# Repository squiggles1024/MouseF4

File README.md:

# Custom Gaming Mouse Project

One of my earlier embedded systems projects. A custom gaming mouse with up to 22 programmable buttons. The firmware is a bit rough around the edges, but I learned a lot about wired USB in the process of coding it.
I wrote a short Python script that communicates new settings to a USB endpoint dedicated to this purpose. 

This iteration implements 14 buttons, a mouse wheel, programmable DPI from 100 to 10000, a tricolored LED with 4 flashing modes, and button keybinds saved in an eeprom.

PCB is my own design featuring an STM32F4 microcontroller which I flashed using a J-Link SEGGER. The PMW3360 motion sensor was purchased as a COTs module. I would have liked to include this on the main PCBA, but the manufacturer was unrespsonsive to my emails and they don't stock the part openly at online retailers like digikey and mouser. The complete BOM and schematics are part of this repository

The 3D printed housing (also my design) was glued to the base plate with E6000. Not a particularly robust mechanical design, but it worked for me. The main issue with this is that, because I didn't write a custom bootloader, the device can no longer be programmed again. This isn't a huge issue, but the mouse wheel you see in the photo is actually "backwards" (Scrolling forward will scroll down, and scrolling backward will scroll up). This is an easy firmware fix, but I can no longer access the JTAG pins or BOOT switch. 

The LED can't really be seen in normal operation, though it can serve as a visual cue that new settings were successfully programmed when changing the keybinds using the python script.

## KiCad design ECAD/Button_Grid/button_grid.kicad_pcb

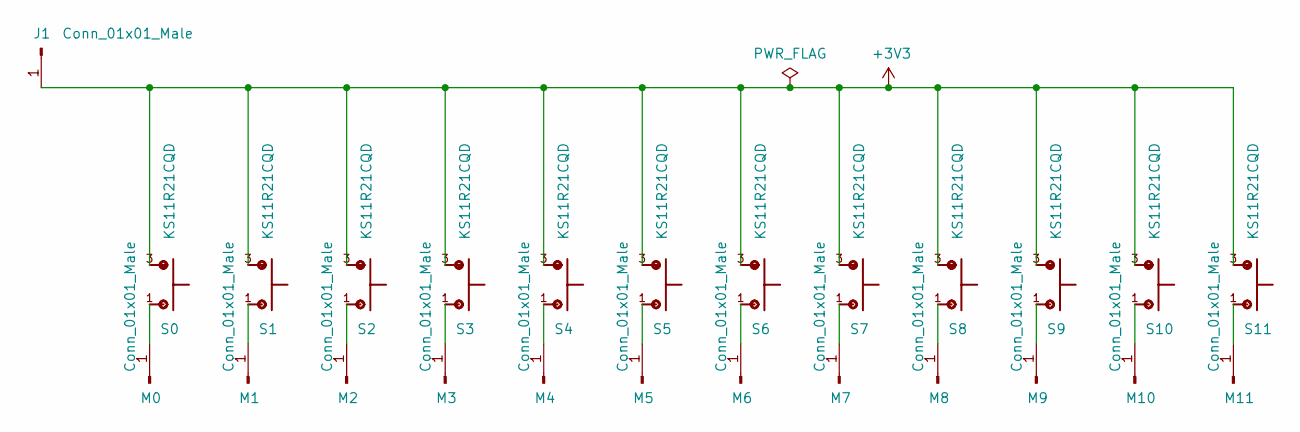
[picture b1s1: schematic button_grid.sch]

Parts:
J1: Conn_01x01_Male; PinHeader_1x01_P2.54mm_Vertical
M0, M1, M2, M3, M4, M5, M6, M7, M8, M9, M10, M11: Conn_01x01_Male; PinHeader_1x01_P2.54mm_Vertical
S0, S1, S2, S3, S4, S5, S6, S7, S8, S9, S10, S11: KS11R21CQD; SW_KS11R21CQD

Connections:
+3V3: J1.1, S0.3, S1.3, S2.3, S3.3, S4.3, S5.3, S6.3, S7.3, S8.3, S9.3, S10.3, S11.3
unnamed: M0.1, S0.1
unnamed: M1.1, S1.1
unnamed: M2.1, S2.1
unnamed: M3.1, S3.1
unnamed: M4.1, S4.1
unnamed: M5.1, S5.1
unnamed: M6.1, S6.1
unnamed: M7.1, S7.1
unnamed: M8.1, S8.1
unnamed: M9.1, S9.1
unnamed: M10.1, S10.1
unnamed: M11.1, S11.1

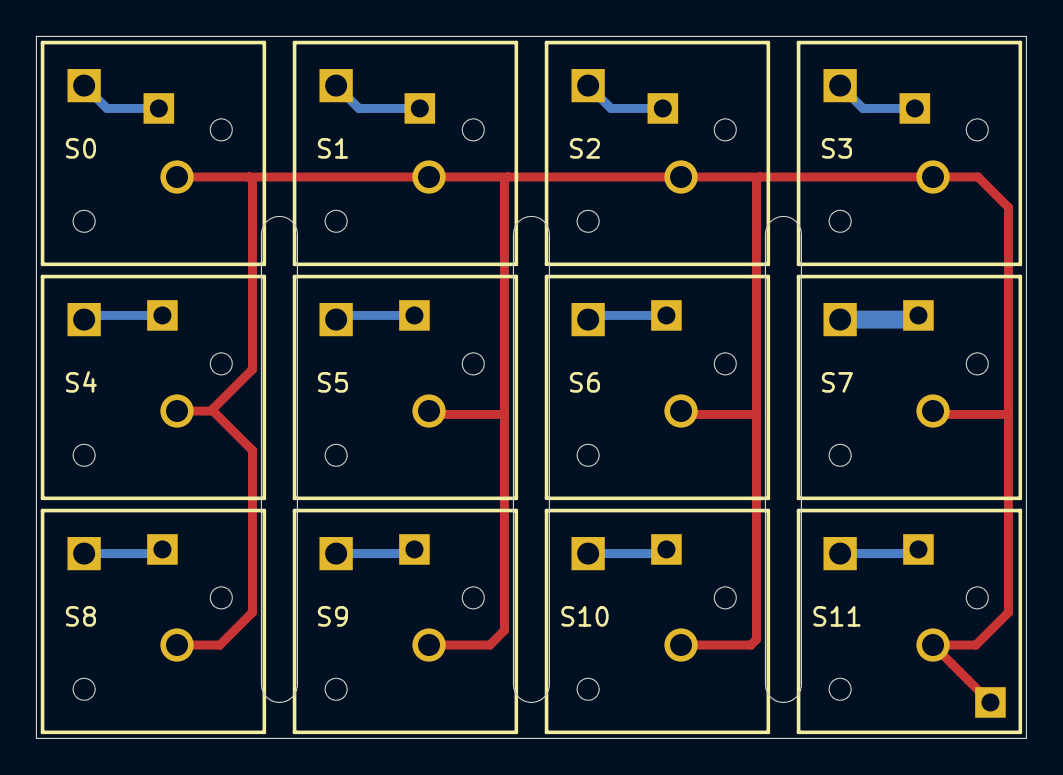
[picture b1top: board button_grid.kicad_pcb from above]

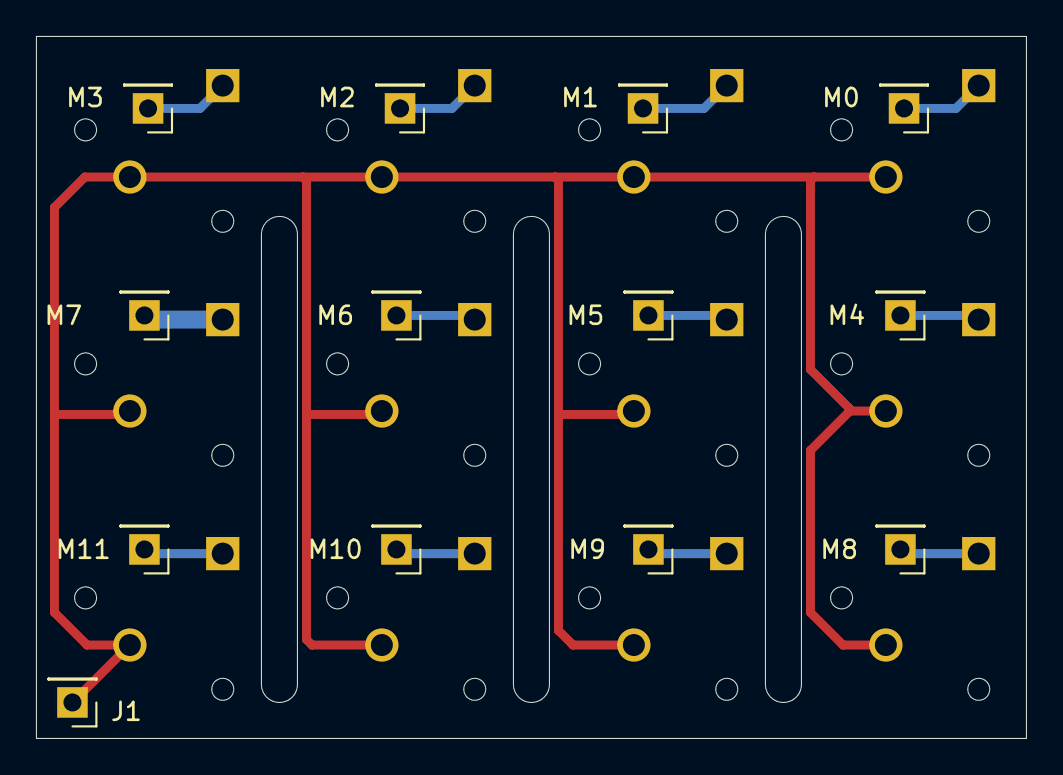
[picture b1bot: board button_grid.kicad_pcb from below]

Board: 2 copper layers, 55.0 x 39.0 mm, 25 parts (13 on the bottom side), 13 nets.

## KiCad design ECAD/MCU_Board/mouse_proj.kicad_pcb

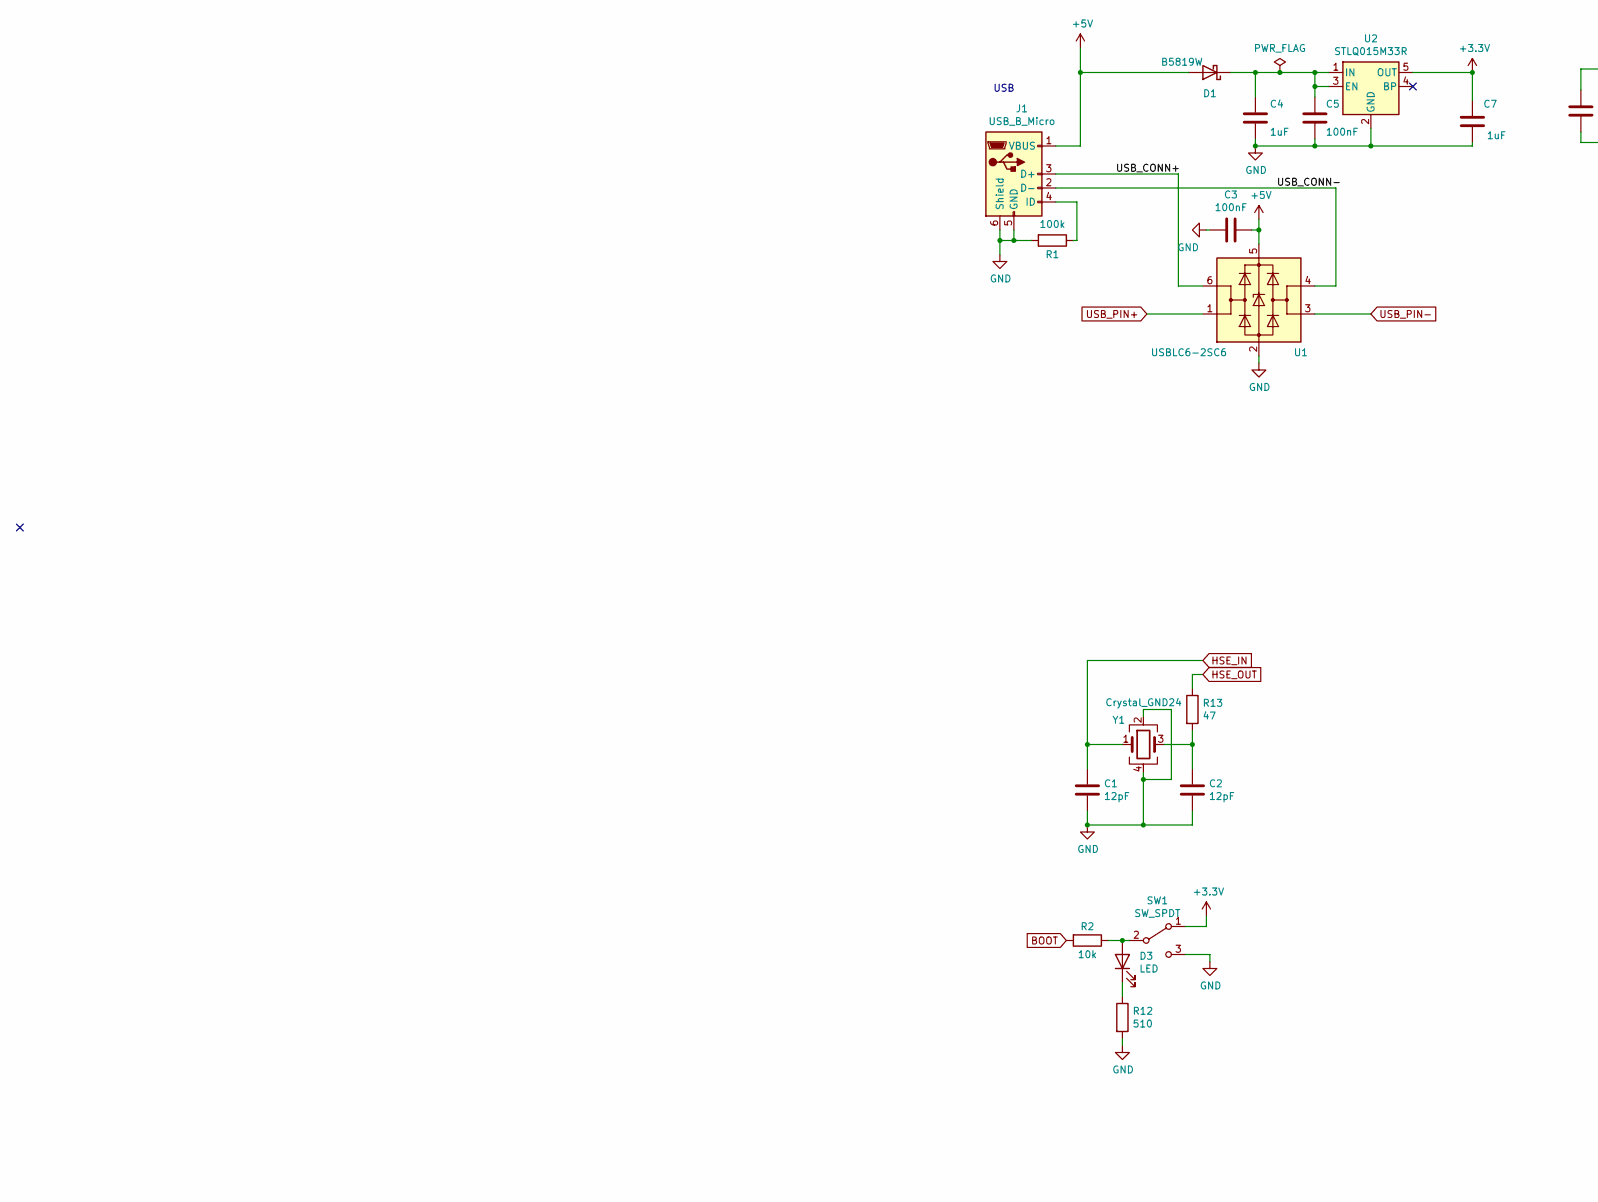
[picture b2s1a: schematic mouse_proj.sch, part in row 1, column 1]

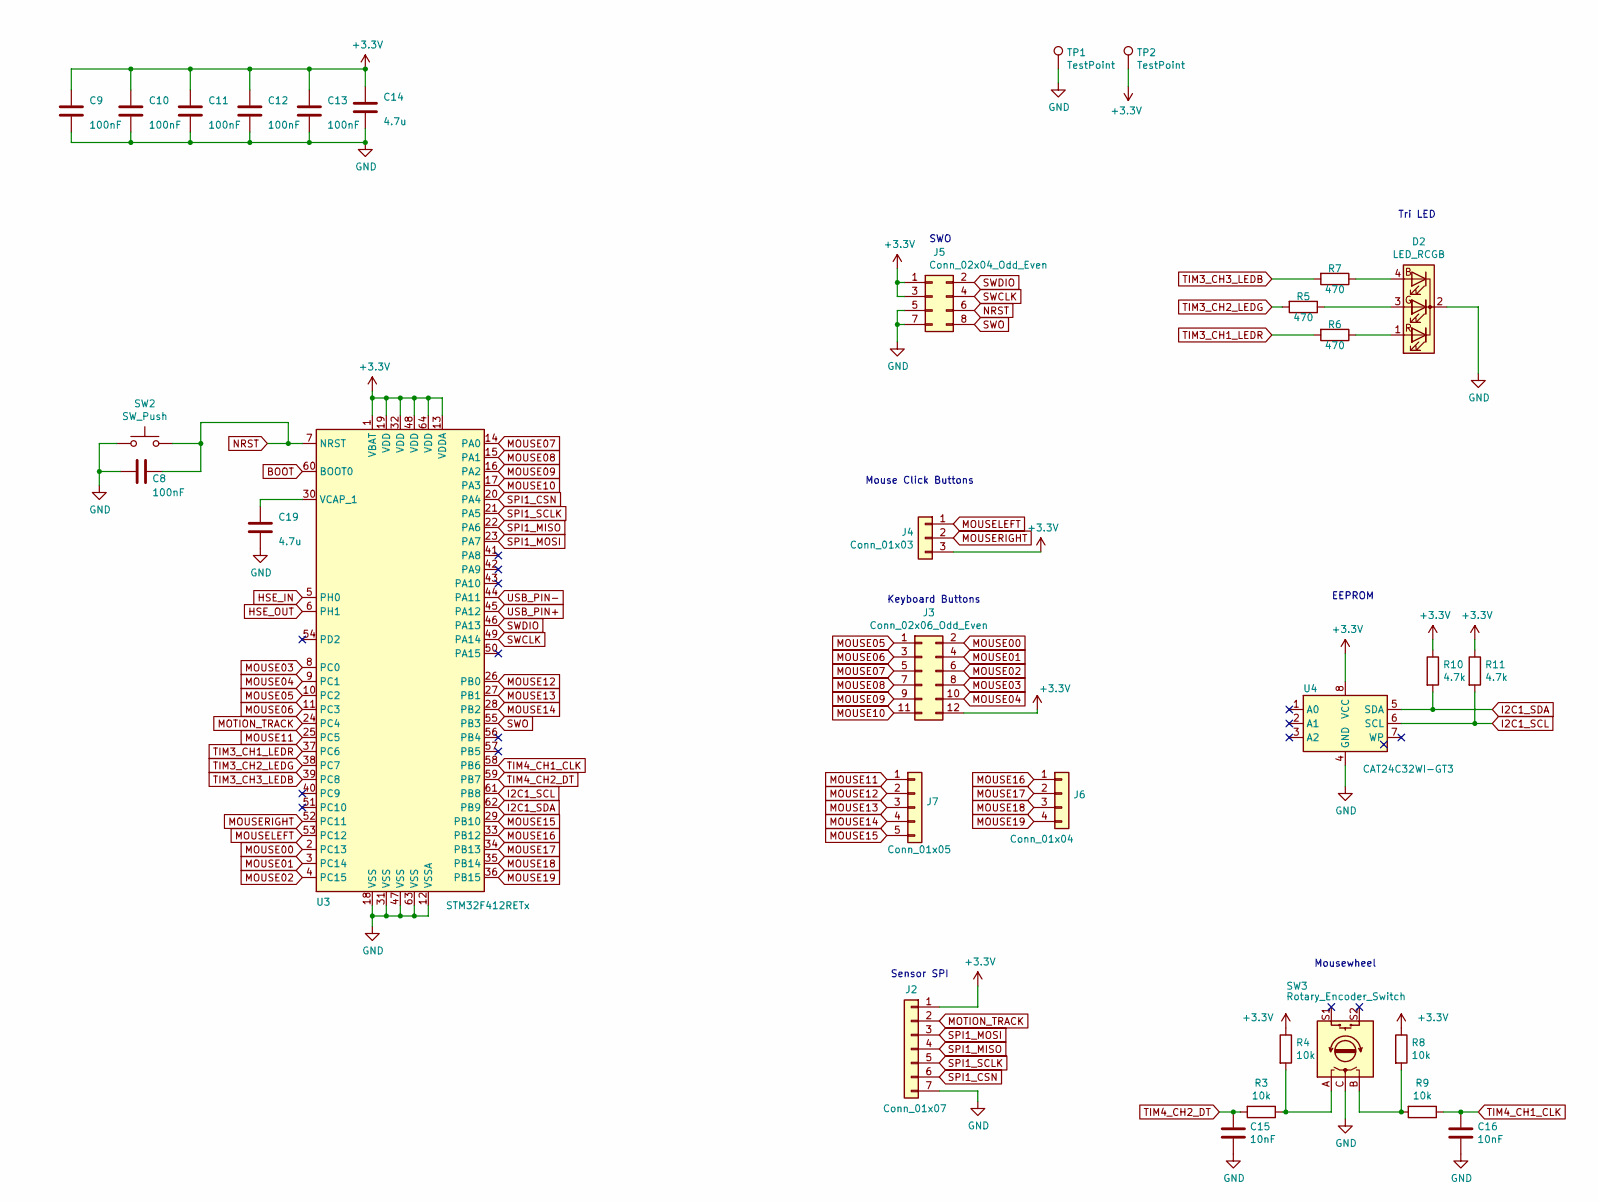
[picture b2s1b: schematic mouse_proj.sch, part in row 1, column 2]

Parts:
C1, C2: 12pF; C_0402_1005Metric; LCSC Part # C26406
C3, C5: 100nF; C_0603_1608Metric; LCSC Part # C14663
C4: 1uF; C_0603_1608Metric; LCSC Part # C15849
C7: 1uF; C_0402_1005Metric; LCSC Part # C52923
C8, C9, C10, C11, C12, C13: 100nF; C_0402_1005Metric; LCSC Part # C307331
C14, C19: 4.7u; C_0402_1005Metric; LCSC Part # C23733
C15, C16: 10nF; C_0402_1005Metric; LCSC Part # C15195
D1: B5819W; D_SOD-123; LCSC Part # C8598
D2: LED_RCGB; LED_D5.0mm-4_RGB_Wide_Pins
D3: LED; D_0603_1608Metric; LCSC Part # C2286
J1: USB_B_Micro; USB_Micro-B_Molex-105017-0001; LCSC Part # C132563
J2: Conn_01x07; PinHeader_1x07_P2.54mm_Vertical
J3: Conn_02x06_Odd_Even; PinHeader_2x06_P2.54mm_Vertical
J4: Conn_01x03; PinHeader_1x03_P2.54mm_Vertical
J5: Conn_02x04_Odd_Even; PinHeader_2x04_P2.54mm_Vertical
J6: Conn_01x04; PinHeader_1x04_P2.54mm_Vertical
J7: Conn_01x05; PinHeader_1x05_P2.54mm_Vertical
R1: 100k; R_0402_1005Metric; LCSC Part # C25741
R2, R3, R4, R8, R9: 10k; R_0402_1005Metric; LCSC Part # C25744
R5, R6, R7: 470; R_0402_1005Metric; LCSC Part # C25117
R10, R11: 4.7k; R_0402_1005Metric; LCSC Part # C25900
R12: 510; R_0402_1005Metric; LCSC Part # C25123
R13: 47; R_0402_1005Metric; LCSC Part # C25117
SW1: SW_SPDT; SW_SPDT_PCM12
SW2: SW_Push; SW_PUSH_6mm_H5mm
SW3: Rotary_Encoder_Switch; RotaryEncoder_Alps_EC11E-Switch_Vertical_H20mm
TP1, TP2: TestPoint; TestPoint_THTPad_D3.0mm_Drill1.5mm
U1: USBLC6-2SC6; SOT-23-6; LCSC Part # C7519
U2: STLQ015M33R; SOT-23-5; LCSC Part # C136154
U3: STM32F412RETx; LQFP-64_10x10mm_P0.5mm; LCSC Part # C89374
U4: CAT24C32WI-GT3; SOIC-8_3.9x4.9mm_P1.27mm; LCSC Part # C81193
Y1: Crystal_GND24; Crystal_SMD_3225-4Pin_3.2x2.5mm; LCSC Part # C13738

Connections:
+3V3: C7.1, C9.1, C10.1, C11.1, C12.1, C13.1, C14.1, J2.1, J3.12, J4.3, J5.1, J5.3, R4.1, R8.1, R10.1, R11.1, SW1.1 (A), TP2.1, U2.5 (OUT), U3.1 (VBAT), U3.13 (VDDA), U3.19 (VDD), U3.32 (VDD), U3.48 (VDD), U3.64 (VDD), U4.8 (VCC)
+5V: C3.1, D1.2 (A), J1.1 (VBUS), U1.5 (VBUS)
/USB_CONN+: J1.3 (D+), U1.6 (I/O1)
/USB_CONN-: J1.2 (D-), U1.4 (I/O2)
BOOT: R2.2, U3.60 (BOOT0)
GND: C1.2, C2.2, C3.2, C4.2, C5.2, C7.2, C8.2, C9.2, C10.2, C11.2, C12.2, C13.2, C14.2, C15.2, C16.2, C19.2, D2.2 (K), J1.5 (GND), J1.6 (Shield), J2.7, J5.5, J5.7, R1.2, R12.2, SW1.3 (C), SW2.1, SW3.C, TP1.1, U1.2 (GND), U2.2 (GND), U3.12 (VSSA), U3.18 (VSS), U3.31 (VSS), U3.47 (VSS), U3.63 (VSS), U4.4 (GND), Y1.2, Y1.4
HSE_IN: C1.1, U3.5 (PH0), Y1.1
HSE_OUT: R13.1, U3.6 (PH1)
I2C1_SCL: R11.2, U3.61 (PB8), U4.6 (SCL)
I2C1_SDA: R10.2, U3.62 (PB9), U4.5 (SDA)
MOTION_TRACK: J2.2, U3.24 (PC4)
MOUSE00: J3.2, U3.2 (PC13)
MOUSE01: J3.4, U3.3 (PC14)
MOUSE02: J3.6, U3.4 (PC15)
MOUSE03: J3.8, U3.8 (PC0)
MOUSE04: J3.10, U3.9 (PC1)
MOUSE05: J3.1, U3.10 (PC2)
MOUSE06: J3.3, U3.11 (PC3)
MOUSE07: J3.5, U3.14 (PA0)
MOUSE08: J3.7, U3.15 (PA1)
MOUSE09: J3.9, U3.16 (PA2)
MOUSE10: J3.11, U3.17 (PA3)
MOUSE11: J7.1, U3.25 (PC5)
MOUSE12: J7.2, U3.26 (PB0)
MOUSE13: J7.3, U3.27 (PB1)
MOUSE14: J7.4, U3.28 (PB2)
MOUSE15: J7.5, U3.29 (PB10)
MOUSE16: J6.1, U3.33 (PB12)
MOUSE17: J6.2, U3.34 (PB13)
MOUSE18: J6.3, U3.35 (PB14)
MOUSE19: J6.4, U3.36 (PB15)
MOUSELEFT: J4.1, U3.53 (PC12)
MOUSERIGHT: J4.2, U3.52 (PC11)
NRST: C8.1, J5.6, SW2.2, U3.7 (NRST)
unnamed: C2.1, R13.2, Y1.3
unnamed: C4.1, C5.1, D1.1 (K), U2.1 (IN), U2.3 (EN)
unnamed: C19.1, U3.30 (VCAP_1)
unnamed: D2.1 (RA), R6.1
unnamed: D2.3 (GA), R5.1
unnamed: D2.4 (BA), R7.1
unnamed: D3.1 (K), R12.1
unnamed: D3.2 (A), R2.1, SW1.2 (B)
unnamed: J1.4 (ID), R1.1
unnamed: R3.1, R4.2, SW3.A
unnamed: R8.2, R9.2, SW3.B
SPI1_CSN: J2.6, U3.20 (PA4)
SPI1_MISO: J2.4, U3.22 (PA6)
SPI1_MOSI: J2.3, U3.23 (PA7)
SPI1_SCLK: J2.5, U3.21 (PA5)
SWCLK: J5.4, U3.49 (PA14)
SWDIO: J5.2, U3.46 (PA13)
SWO: J5.8, U3.55 (PB3)
TIM3_CH1_LEDR: R6.2, U3.37 (PC6)
TIM3_CH2_LEDG: R5.2, U3.38 (PC7)
TIM3_CH3_LEDB: R7.2, U3.39 (PC8)
TIM4_CH1_CLK: C16.1, R9.1, U3.58 (PB6)
TIM4_CH2_DT: C15.1, R3.2, U3.59 (PB7)
USB_PIN+: U1.1 (I/O1), U3.45 (PA12)
USB_PIN-: U1.3 (I/O2), U3.44 (PA11)

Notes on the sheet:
SWO
Tri LED
EEPROM
Mousewheel
Keyboard Buttons
Mouse Click Buttons
Sensor SPI
USB

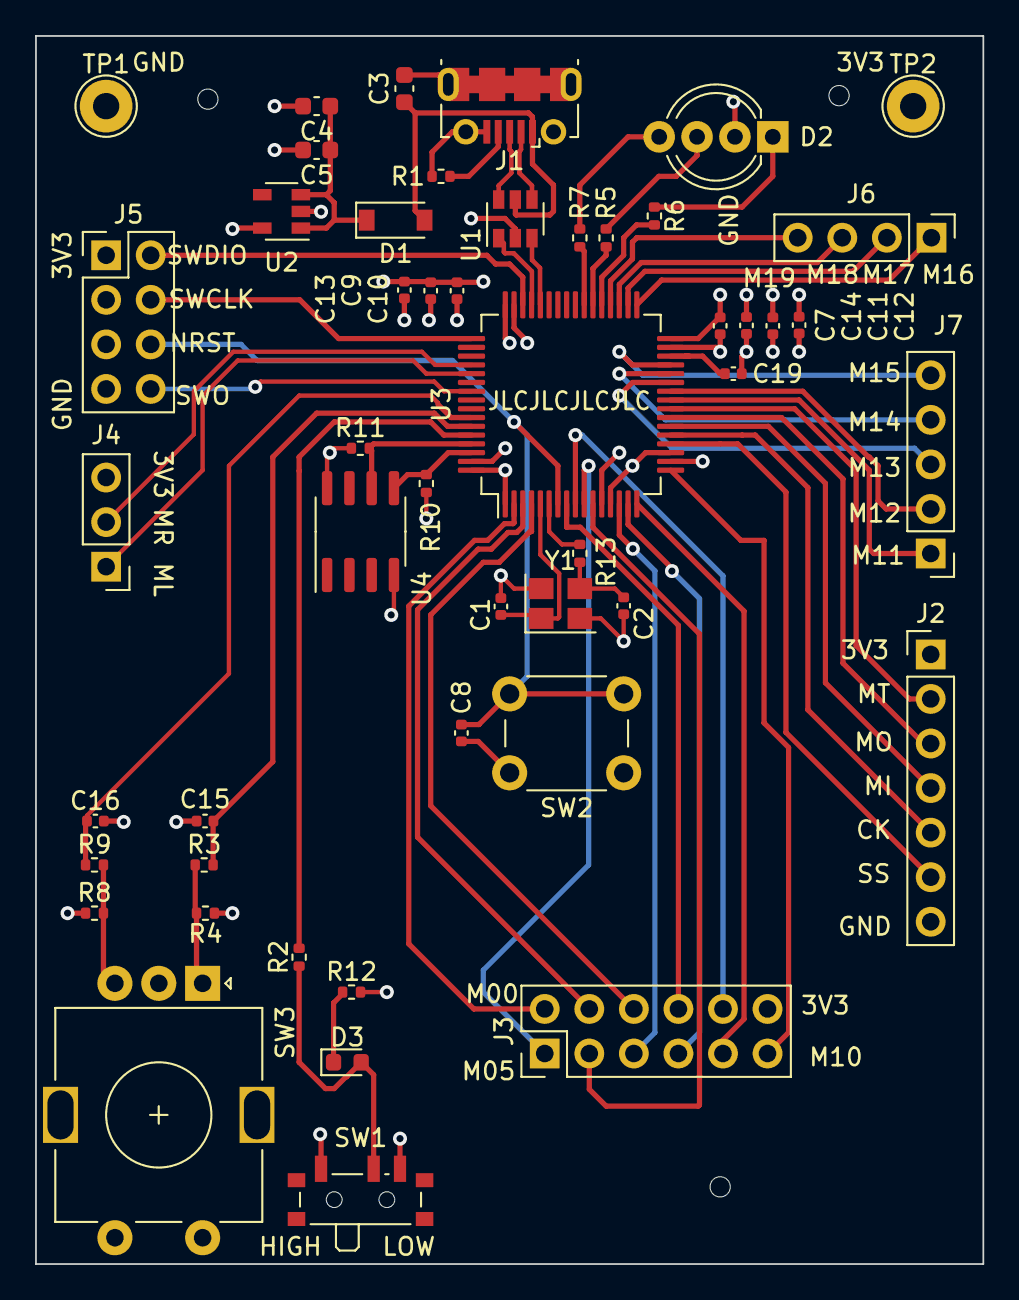
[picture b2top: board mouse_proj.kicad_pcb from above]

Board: 4 copper layers, 54.0 x 70.0 mm, 49 parts (0 on the bottom side), 59 nets.

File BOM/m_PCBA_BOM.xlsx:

Comment | Designator | Footprint | JLCPCB Part #（optional） | Other PN
12pF | C1 | Capacitor_SMD:C_0402_1005Metric | C26406
12pF | C2 | Capacitor_SMD:C_0402_1005Metric | C26406
100nF | C3 | Capacitor_SMD:C_0603_1608Metric | C14663
1uF | C4 | Capacitor_SMD:C_0603_1608Metric | C15849
100nF | C5 | Capacitor_SMD:C_0603_1608Metric | C14663
1uF | C7 | Capacitor_SMD:C_0402_1005Metric | C52923
100nF | C8 | Capacitor_SMD:C_0402_1005Metric | C307331
100nF | C9 | Capacitor_SMD:C_0402_1005Metric | C307331
100nF | C10 | Capacitor_SMD:C_0402_1005Metric | C307331
100nF | C11 | Capacitor_SMD:C_0402_1005Metric | C307331
100nF | C12 | Capacitor_SMD:C_0402_1005Metric | C307331
100nF | C13 | Capacitor_SMD:C_0402_1005Metric | C307331
4.7u | C14 | Capacitor_SMD:C_0402_1005Metric | C23733
10nF | C15 | Capacitor_SMD:C_0402_1005Metric | C15195
10nF | C16 | Capacitor_SMD:C_0402_1005Metric | C15195
4.7u | C19 | Capacitor_SMD:C_0402_1005Metric | C23733
B5819W | D1 | Diode_SMD:D_SOD-123 | C8598
LED_RCGB | D2 | LED_THT:LED_D5.0mm-4_RGB_Wide_Pins |  | COM-00105
LED | D3 | Diode_SMD:D_0603_1608Metric | C2286
USB_B_Micro | J1 | Connector_USB:USB_Micro-B_Molex-105017-0001 | C132563
Conn_01x07 | J2 | Connector_PinHeader_2.54mm:PinHeader_1x07_P2.54mm_Vertical
Conn_02x06_Odd_Even | J3 | Connector_PinHeader_2.54mm:PinHeader_2x06_P2.54mm_Vertical
Conn_01x03 | J4 | Connector_PinHeader_2.54mm:PinHeader_1x03_P2.54mm_Vertical
Conn_02x04_Odd_Even | J5 | Connector_PinHeader_2.54mm:PinHeader_2x04_P2.54mm_Vertical
Conn_01x04 | J6 | Connector_PinHeader_2.54mm:PinHeader_1x04_P2.54mm_Vertical
Conn_01x05 | J7 | Connector_PinHeader_2.54mm:PinHeader_1x05_P2.54mm_Vertical
100k | R1 | Resistor_SMD:R_0402_1005Metric | C25741
10k | R2 | Resistor_SMD:R_0402_1005Metric | C25744
10k | R3 | Resistor_SMD:R_0402_1005Metric | C25744
10k | R4 | Resistor_SMD:R_0402_1005Metric | C25744
470 | R5 | Resistor_SMD:R_0402_1005Metric | C25117
470 | R6 | Resistor_SMD:R_0402_1005Metric | C25117
470 | R7 | Resistor_SMD:R_0402_1005Metric | C25117
10k | R8 | Resistor_SMD:R_0402_1005Metric | C25744
10k | R9 | Resistor_SMD:R_0402_1005Metric | C25744
4.7k | R10 | Resistor_SMD:R_0402_1005Metric | C25900
4.7k | R11 | Resistor_SMD:R_0402_1005Metric | C25900
510 | R12 | Resistor_SMD:R_0402_1005Metric | C25123
47 | R13 | Resistor_SMD:R_0402_1005Metric | C25117
SW_SPDT | SW1 | Button_Switch_SMD:SW_SPDT_PCM12 |  | PCM12SMTR
SW_Push | SW2 | Button_Switch_THT:SW_PUSH_6mm_H5mm |  | Any 6x5 push button
Rotary_Encoder_Switch | SW3 | Rotary_Encoder:RotaryEncoder_Alps_EC11E-Switch_Vertical_H20mm |  | EC11E09244AQ
USBLC6-2SC6 | U1 | Package_TO_SOT_SMD:SOT-23-6 | C7519
STLQ015M33R | U2 | Package_TO_SOT_SMD:SOT-23-5 | C136154
STM32F412RETx | U3 | Package_QFP:LQFP-64_10x10mm_P0.5mm | C89374
CAT24C32WI-GT3 | U4 | Package_SO:SOIC-8_3.9x4.9mm_P1.27mm | C81193
Crystal_GND24 | Y1 | Crystal:Crystal_SMD_3225-4Pin_3.2x2.5mm | C13738

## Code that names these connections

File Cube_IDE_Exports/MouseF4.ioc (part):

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PA2.GPIO_PuPd=GPIO_PULLDOWN
PB13.GPIOParameters=GPIO_PuPd,GPIO_Label
PA6.Mode=Full_Duplex_Master
PC7.GPIOParameters=GPIO_Label
Mcu.UserName=STM32F412RETx
PB10.GPIO_PuPd=GPIO_PULLDOWN
PC12.Signal=GPIO_Input
PB14.GPIO_Label=MOUSE18
PA3.GPIO_PuPd=GPIO_PULLDOWN
PA0.GPIO_Label=MOUSE07
PC0.GPIOParameters=GPIO_PuPd,GPIO_Label
PC0.GPIO_Label=MOUSE03
PC6.GPIO_Label=TIM3_CH1_LEDR
PA11.Mode=Device_Only
PA3.GPIOParameters=GPIO_PuPd,GPIO_Label
PB0.GPIO_Label=MOUSE12
PB6.GPIO_Label=TIM4_CH1_CLK
PC13.GPIO_Label=MOUSE00
PB13.GPIO_Label=MOUSE17
PB13.Signal=GPIO_Input
PB15.Signal=GPIO_Input
PA2.GPIOParameters=GPIO_PuPd,GPIO_Label
PC15-OSC32_OUT.GPIO_Label=MOUSE02
RCC.SYSCLKSource=RCC_SYSCLKSOURCE_PLLCLK
PC11.GPIO_PuPd=GPIO_PULLDOWN
PA12.Signal=USB_OTG_FS_DP
PH0\ -\ OSC_IN.Signal=RCC_OSC_IN
PC1.GPIOParameters=GPIO_PuPd,GPIO_Label
PB1.GPIO_PuPd=GPIO_PULLDOWN
PB6.Signal=S_TIM4_CH1
PC7.Signal=S_TIM3_CH2
PC3.Signal=GPIO_Input
PA1.GPIO_PuPd=GPIO_PULLDOWN
RCC.HSE_VALUE=16000000
PA4.GPIO_PuPd=GPIO_PULLUP
PB2.Signal=GPIO_Input
PC1.GPIO_PuPd=GPIO_PULLDOWN
PA4.GPIO_Speed=GPIO_SPEED_FREQ_VERY_HIGH
PB12.GPIO_Label=MOUSE16
PB0.GPIOParameters=GPIO_PuPd,GPIO_Label
PA1.GPIOParameters=GPIO_PuPd,GPIO_Label
PC4.GPIO_Label=MOTION_TRACK
PA14.Mode=Serial_Wire
PA5.GPIO_PuPd=GPIO_PULLUP
PB1.GPIO_Label=MOUSE13
PC11.GPIO_Label=MOUSERIGHT
PC13.GPIO_PuPd=GPIO_PULLDOWN
PB7.Signal=S_TIM4_CH2
PB6.GPIOParameters=GPIO_Label
PB2.GPIO_PuPd=GPIO_PULLDOWN
PC14-OSC32_IN.GPIOParameters=GPIO_PuPd,GPIO_Label
PA0.Signal=GPIO_Input
PB7.GPIO_Label=TIM4_CH2_DT
PC8.GPIOParameters=GPIO_Label
Mcu.Package=LQFP64
PB9.Signal=I2C1_SDA
PB1.Signal=GPIO_Input
PA6.Signal=SPI1_MISO
PB14.GPIO_PuPd=GPIO_PULLDOWN
PB15.GPIO_PuPd=GPIO_PULLDOWN
PA0.GPIO_PuPd=GPIO_PULLDOWN
PA2.GPIO_Label=MOUSE09
PA5.GPIOParameters=GPIO_PuPd
PB14.GPIOParameters=GPIO_PuPd,GPIO_Label
PC14-OSC32_IN.GPIO_Label=MOUSE01
PC5.Signal=GPIO_Input
PB10.GPIOParameters=GPIO_PuPd,GPIO_Label
PC12.GPIO_PuPd=GPIO_PULLDOWN
PC15-OSC32_OUT.GPIOParameters=GPIO_PuPd,GPIO_Label
PC0.GPIO_PuPd=GPIO_PULLDOWN
PA4.GPIO_Label=SP1_CSN
PC2.GPIO_Label=MOUSE05
PC4.GPIOParameters=GPIO_Label
PA3.Signal=GPIO_Input
PA5.Mode=Full_Duplex_Master
PA7.Mode=Full_Duplex_Master
PC13.Signal=GPIO_Input
PC11.Signal=GPIO_Input
PH1\ -\ OSC_OUT.Mode=HSE-External-Oscillator
PC8.Signal=S_TIM3_CH3
PC2.Signal=GPIO_Input
PC4.Signal=GPIO_Input
PC6.Signal=S_TIM3_CH1
PC0.Signal=GPIO_Input
PC14-OSC32_IN.Signal=GPIO_Input
PC5.GPIO_PuPd=GPIO_PULLDOWN
PC11.GPIOParameters=GPIO_PuPd,GPIO_Label
PC3.GPIOParameters=GPIO_PuPd,GPIO_Label
PC8.GPIO_Label=TIM3_CH3_LEDB
PC12.GPIOParameters=GPIO_PuPd,GPIO_Label
PA13.Signal=SYS_JTMS-SWDIO
PH0\ -\ OSC_IN.Mode=HSE-External-Oscillator
PA4.PinState=GPIO_PIN_SET
PB10.GPIO_Label=MOUSE15
PB7.GPIOParameters=GPIO_Label
PC5.GPIOParameters=GPIO_PuPd,GPIO_Label
PB9.Mode=I2C
PB2.GPIOParameters=GPIO_PuPd,GPIO_Label
PC15-OSC32_OUT.Signal=GPIO_Input
PA1.Signal=GPIO_Input
PB10.Signal=GPIO_Input
PB14.Signal=GPIO_Input
PA5.Signal=SPI1_SCK
PH1\ -\ OSC_OUT.Signal=RCC_OSC_OUT
board=custom
PB13.GPIO_PuPd=GPIO_PULLDOWN
PB15.GPIO_Label=MOUSE19
PC13.GPIOParameters=GPIO_PuPd,GPIO_Label
PC2.GPIOParameters=GPIO_PuPd,GPIO_Label
PC1.GPIO_Label=MOUSE04
PA1.GPIO_Label=MOUSE08
PC15-OSC32_OUT.GPIO_PuPd=GPIO_PULLDOWN
PA4.GPIOParameters=GPIO_Speed,PinState,GPIO_PuPd,GPIO_Label
PC2.GPIO_PuPd=GPIO_PULLDOWN
PB15.GPIOParameters=GPIO_PuPd,GPIO_Label
PA13.Mode=Serial_Wire
Mcu.Name=STM32F412R(E-G)Tx
PA2.Signal=GPIO_Input
PC7.GPIO_Label=TIM3_CH2_LEDG
PA4.Signal=GPIO_Output
RCC.SYSCLKFreq_VALUE=72000000
PA12.Mode=Device_Only
PC5.GPIO_Label=MOUSE11
PC12.GPIO_Label=MOUSELEFT
PA11.Signal=USB_OTG_FS_DM
PA14.Signal=SYS_JTCK-SWCLK
PB2.GPIO_Label=MOUSE14
PA0.GPIOParameters=GPIO_PuPd,GPIO_Label
PC6.GPIOParameters=GPIO_Label
PB8.Mode=I2C
PB8.Signal=I2C1_SCL
PC3.GPIO_Label=MOUSE06
PC14-OSC32_IN.GPIO_PuPd=GPIO_PULLDOWN
PB12.GPIO_PuPd=GPIO_PULLDOWN
PB0.Signal=GPIO_Input
PC1.Signal=GPIO_Input
PB12.GPIOParameters=GPIO_PuPd,GPIO_Label
PB12.Signal=GPIO_Input
PB0.GPIO_PuPd=GPIO_PULLDOWN
PC3.GPIO_PuPd=GPIO_PULLDOWN
PA3.GPIO_Label=MOUSE10
PB1.GPIOParameters=GPIO_PuPd,GPIO_Label
PA7.Signal=SPI1_MOSI

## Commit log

2021-11-30 Removed commented code; added VTOR fix
2021-11-30 Added BOM
2021-11-30 Added Mechanical models
2021-11-30 Added ECAD Models
2021-11-30 Added python script for key rebind
2022-12-01 Remove VTOR Relocation line from main.
2022-12-01 Add Readme photos
